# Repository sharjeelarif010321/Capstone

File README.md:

# Capstone
Final year capstone project

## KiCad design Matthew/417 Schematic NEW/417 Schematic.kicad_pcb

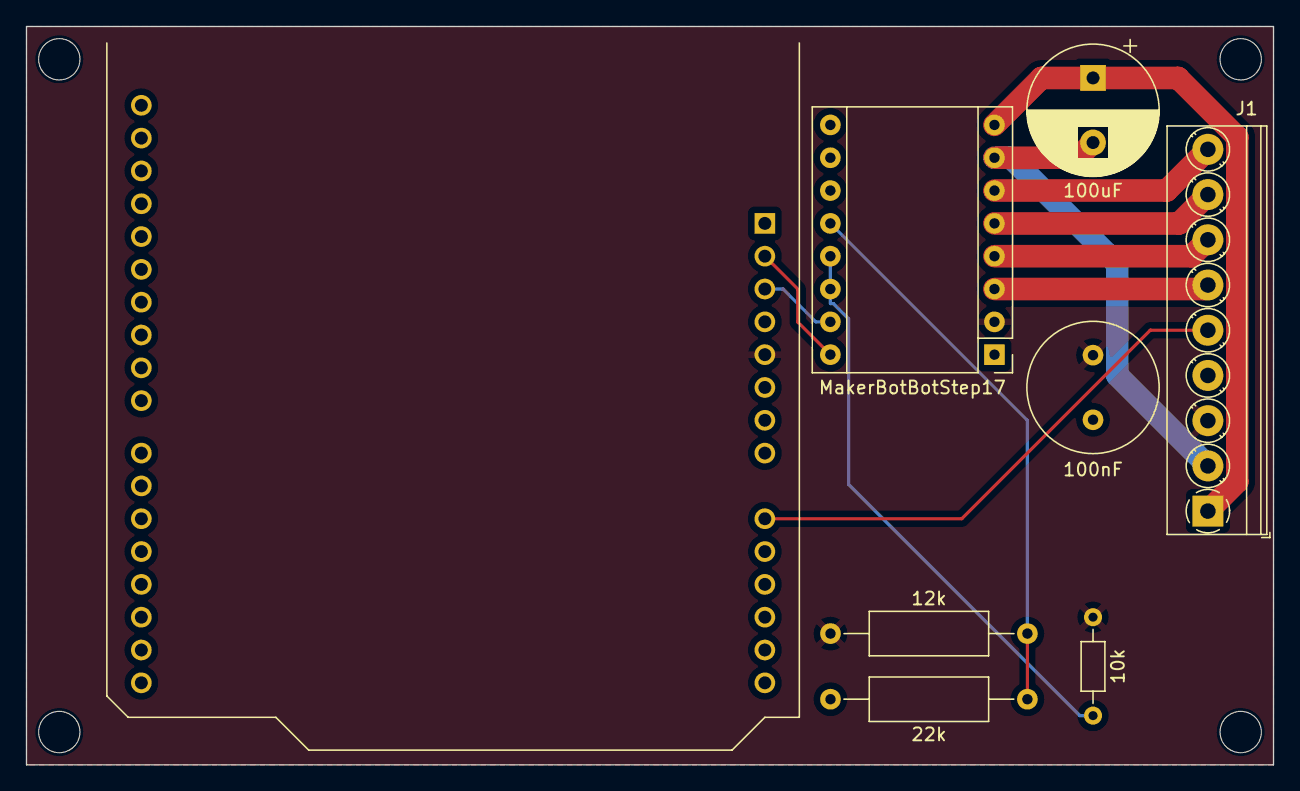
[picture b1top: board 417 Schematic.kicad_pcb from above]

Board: 2 copper layers, 96.5 x 57.2 mm, 12 parts (0 on the bottom side), 13 nets.

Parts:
10k: 10k; R_Axial_DIN0204_L3.6mm_D1.6mm_P7.62mm_Horizontal
12k: 12k; R_Axial_DIN0309_L9.0mm_D3.2mm_P15.24mm_Horizontal
22k: 22k; R_Axial_DIN0309_L9.0mm_D3.2mm_P15.24mm_Horizontal
100nF: physically close to board; C_Radial_D10.0mm_H12.5mm_P5.00mm
100uF: physically close to board; CP_Radial_D10.0mm_P5.00mm
A1: Arduino_UNO_R3
J1: Screw_Terminal_01x09; TerminalBlock_Phoenix_PT-1,5-9-3.5-H_1x09_P3.50mm_Horizontal
MakerBotBotStep17: A4982; Pololu_Breakout-16_15.2x20.3mm
REF01, REF02, REF03, REF04: MountingHole_3.2mm_M3

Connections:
+5V: 10k.1, 12k.1, 100nF.1, A1.5 (+5V), J1.3, MakerBotBotStep17.2 (VDD)
GND: 22k.2, 100nF.2, A1.6 (GND), A1.7 (GND), A1.29 (GND), J1.4, MakerBotBotStep17.1 (GND)
unnamed: A1.9 (A0), J1.5
unnamed: A1.2 (IOREF), MakerBotBotStep17.16 (DIR)
unnamed: A1.3 (~RESET), MakerBotBotStep17.15 (STEP)
unnamed: 100uF.1, J1.1, MakerBotBotStep17.8 (VMOT)
unnamed: 100uF.2, J1.2, MakerBotBotStep17.7 (GND)
unnamed: J1.6, MakerBotBotStep17.3 (1B)
unnamed: J1.7, MakerBotBotStep17.4 (1A)
unnamed: J1.8, MakerBotBotStep17.5 (2A)
unnamed: J1.9, MakerBotBotStep17.6 (2B)
unnamed: 12k.2, 22k.1, MakerBotBotStep17.12 (VR)
unnamed: 10k.2, MakerBotBotStep17.13 (~RESET), MakerBotBotStep17.14 (~SLEEP)

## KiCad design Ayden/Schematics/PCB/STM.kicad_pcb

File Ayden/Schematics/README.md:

This directory contains all schematics for the Baby Safety Subsystem, created in KiCAD.
<br>
<br>
**/PCB/** is the schematic used to design the PCB.
<br>
<br>
**/PCB_backwards_STM/** is an identical schematic to the previous, with the STM32F103RB's footprint mirrored on the PCB layout.
This was the first layout for the PCB I created, but I realized that the rear pins on my STM32F103RB board were bent, which means the STM board would not have been able to mount to the PCB properly.
<br>
<br>
**/STM/** is the schematic that shows the entire circuit, including the layout of the pressure mat. Since the previous two schematics have only a terminal block, it is not easy to visualize the connection to the pressure mat. This schematic does not include any PCB layout.
<br>
<br>
**/Wearable/** is the schematic for the wearable heart rate and blood oxygen monitor. A PCB was not necessary for this schematic.
<br>
<br>
**/libraries/** contains the two custom libraries that were necessary for me to get proper footprints for all of my components.

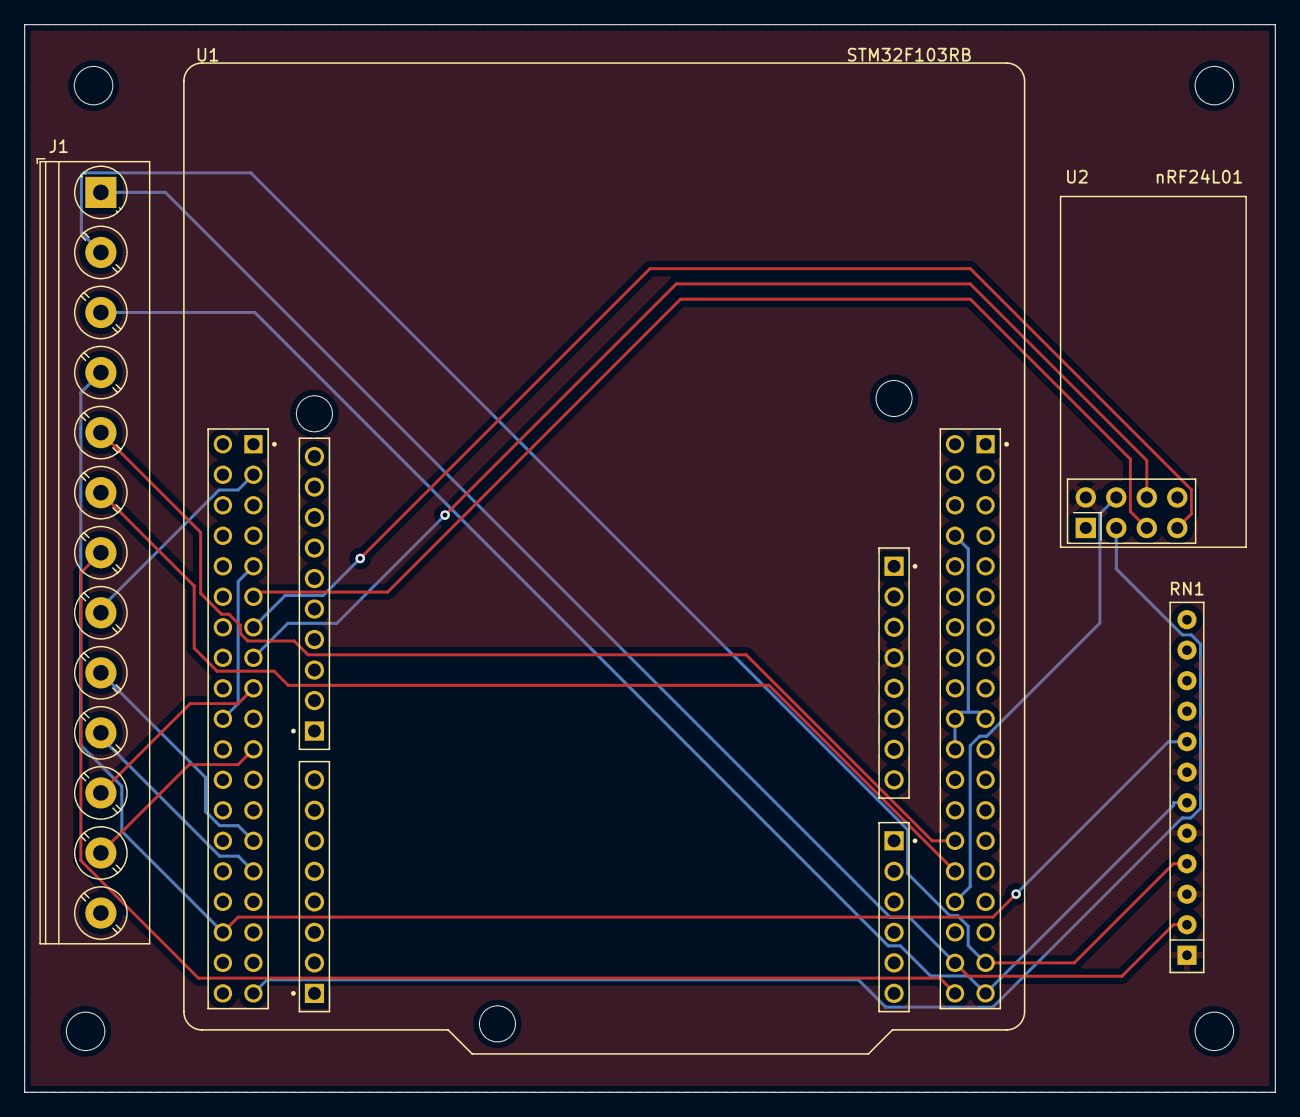
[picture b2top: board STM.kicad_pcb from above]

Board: 2 copper layers, 104.1 x 88.9 mm, 8 parts (1 on the bottom side), 21 nets.

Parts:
J1: Screw_Terminal_01x13; TerminalBlock_Phoenix_PT-1,5-13-5.0-H_1x13_P5.00mm_Horizont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
REF01, REF02, REF03, REF04: MountingHole_3.2mm_M3
RN1: R_Pack_SIP_1k; R_Array_SIP12
U1: NUCLEO-F103RB; ST_NUCLEO-F303RE
U2: NRF24L01_Breakout; nRF24L01_Breakout

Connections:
+3.3V: RN1.1 (R1.1), RN1.3 (R2.1), RN1.5 (R3.1), RN1.7 (R4.1), U1.CN6_4 (+3V3), U2.2 (VCC)
GND: J1.13, U1.CN6_6 (GND), U1.CN6_7 (GND), U2.1 (GND)
unnamed: J1.1, RN1.2 (R1.2), U1.CN7_36 (PC1)
unnamed: J1.2, RN1.4 (R2.2), U1.CN7_35 (PC2)
unnamed: J1.3, RN1.6 (R3.2), U1.CN7_37 (PC3)
unnamed: J1.4, RN1.8 (R4.2), U1.CN10_34 (PC4)
unnamed: U1.CN7_8 (GND_S1), U1.CN7_19 (GND_S1), U1.CN7_20 (GND_S1), U1.CN7_22 (GND_S1)
unnamed: J1.5, U1.CN7_28 (PA0)
unnamed: J1.6, U1.CN7_30 (PA1)
unnamed: U1.CN7_32 (PA4), U2.4 (~CSN)
unnamed: J1.7, U1.CN7_38 (PC0)
unnamed: J1.8, U1.CN10_3 (PB8)
unnamed: U1.CN10_11 (PA5), U2.5 (SCK)
unnamed: U1.CN10_13 (PA6), U2.7 (MISO)
unnamed: U1.CN10_15 (PA7), U2.6 (MOSI)
unnamed: J1.11, U1.CN10_17 (PB6)
unnamed: U1.CN10_9 (GND_S2), U1.CN10_20 (GND_S2)
unnamed: J1.12, U1.CN10_21 (PA9)
unnamed: J1.9, U1.CN10_27 (PB4)
unnamed: J1.10, U1.CN10_29 (PB5)
unnamed: U1.CN10_37 (PA3), U2.3 (CE)

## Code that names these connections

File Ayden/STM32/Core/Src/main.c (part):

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  GPIO_InitStruct.Pull = GPIO_NOPULL;
  HAL_GPIO_Init(B1_GPIO_Port, &GPIO_InitStruct);

  /*Configure GPIO pins : PC0 PC8 */
  GPIO_InitStruct.Pin = GPIO_PIN_0|GPIO_PIN_8;
  GPIO_InitStruct.Mode = GPIO_MODE_OUTPUT_PP;
  GPIO_InitStruct.Pull = GPIO_NOPULL;
  GPIO_InitStruct.Speed = GPIO_SPEED_FREQ_LOW;
  HAL_GPIO_Init(GPIOC, &GPIO_InitStruct);

  /*Configure GPIO pins : PA0 PA1 PA3 PA4 */
  GPIO_InitStruct.Pin = GPIO_PIN_0|GPIO_PIN_1|GPIO_PIN_3|GPIO_PIN_4;
  GPIO_InitStruct.Mode = GPIO_MODE_OUTPUT_PP;
  GPIO_InitStruct.Pull = GPIO_NOPULL;
  GPIO_InitStruct.Speed = GPIO_SPEED_FREQ_LOW;
  HAL_GPIO_Init(GPIOA, &GPIO_InitStruct);

  /*Configure GPIO pins : PB4 PB5 PB6 PB8 */
  GPIO_InitStruct.Pin = GPIO_PIN_4|GPIO_PIN_5|GPIO_PIN_6|GPIO_PIN_8;
  GPIO_InitStruct.Mode = GPIO_MODE_OUTPUT_PP;
  GPIO_InitStruct.Pull = GPIO_NOPULL;
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
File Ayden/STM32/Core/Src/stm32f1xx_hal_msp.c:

/* USER CODE BEGIN Header */
/**
  ******************************************************************************
  * @file         stm32f1xx_hal_msp.c
  * @brief        This file provides code for the MSP Initialization
  *               and de-Initialization codes.
  ******************************************************************************
  * @attention
  *
  * Copyright (c) 2023 STMicroelectronics.
  * All rights reserved.
  *
  * This software is licensed under terms that can be found in the LICENSE file
  * in the root directory of this software component.
  * If no LICENSE file comes with this software, it is provided AS-IS.
  *
  ******************************************************************************
  */
/* USER CODE END Header */

/* Includes ------------------------------------------------------------------*/
#include "main.h"
/* USER CODE BEGIN Includes */

/* USER CODE END Includes */

/* Private typedef -----------------------------------------------------------*/
/* USER CODE BEGIN TD */

/* USER CODE END TD */

/* Private define ------------------------------------------------------------*/
/* USER CODE BEGIN Define */

/* USER CODE END Define */

/* Private macro -------------------------------------------------------------*/
/* USER CODE BEGIN Macro */

/* USER CODE END Macro */

/* Private variables ---------------------------------------------------------*/
/* USER CODE BEGIN PV */

/* USER CODE END PV */

/* Private function prototypes -----------------------------------------------*/
/* USER CODE BEGIN PFP */

/* USER CODE END PFP */

/* External functions --------------------------------------------------------*/
/* USER CODE BEGIN ExternalFunctions */

/* USER CODE END ExternalFunctions */

/* USER CODE BEGIN 0 */

/* USER CODE END 0 */
/**
  * Initializes the Global MSP.
  */
void HAL_MspInit(void)
{
  /* USER CODE BEGIN MspInit 0 */

  /* USER CODE END MspInit 0 */

  __HAL_RCC_AFIO_CLK_ENABLE();
  __HAL_RCC_PWR_CLK_ENABLE();

  /* System interrupt init*/

  /** NOJTAG: JTAG-DP Disabled and SW-DP Enabled
  */
  __HAL_AFIO_REMAP_SWJ_NOJTAG();

  /* USER CODE BEGIN MspInit 1 */

  /* USER CODE END MspInit 1 */
}

/**
* @brief ADC MSP Initialization
* This function configures the hardware resources used in this example
* @param hadc: ADC handle pointer
* @retval None
*/
void HAL_ADC_MspInit(ADC_HandleTypeDef* hadc)
{
  GPIO_InitTypeDef GPIO_InitStruct = {0};
  if(hadc->Instance==ADC1)
  {
  /* USER CODE BEGIN ADC1_MspInit 0 */

  /* USER CODE END ADC1_MspInit 0 */
    /* Peripheral clock enable */
    __HAL_RCC_ADC1_CLK_ENABLE();

    __HAL_RCC_GPIOC_CLK_ENABLE();
    /**ADC1 GPIO Configuration
    PC1     ------> ADC1_IN11
    PC2     ------> ADC1_IN12
    PC3     ------> ADC1_IN13
    PC4     ------> ADC1_IN14
    */
    GPIO_InitStruct.Pin = GPIO_PIN_1|GPIO_PIN_2|GPIO_PIN_3|GPIO_PIN_4;
    GPIO_InitStruct.Mode = GPIO_MODE_ANALOG;
    HAL_GPIO_Init(GPIOC, &GPIO_InitStruct);

  /* USER CODE BEGIN ADC1_MspInit 1 */

  /* USER CODE END ADC1_MspInit 1 */
  }

}

/**
* @brief ADC MSP De-Initialization
* This function freeze the hardware resources used in this example
* @param hadc: ADC handle pointer
* @retval None
*/
void HAL_ADC_MspDeInit(ADC_HandleTypeDef* hadc)
{
  if(hadc->Instance==ADC1)
  {
  /* USER CODE BEGIN ADC1_MspDeInit 0 */

  /* USER CODE END ADC1_MspDeInit 0 */
    /* Peripheral clock disable */
    __HAL_RCC_ADC1_CLK_DISABLE();

    /**ADC1 GPIO Configuration
    PC1     ------> ADC1_IN11
    PC2     ------> ADC1_IN12
    PC3     ------> ADC1_IN13
    PC4     ------> ADC1_IN14
    */
    HAL_GPIO_DeInit(GPIOC, GPIO_PIN_1|GPIO_PIN_2|GPIO_PIN_3|GPIO_PIN_4);

  /* USER CODE BEGIN ADC1_MspDeInit 1 */

  /* USER CODE END ADC1_MspDeInit 1 */
  }

}

/**
* @brief SPI MSP Initialization
* This function configures the hardware resources used in this example
* @param hspi: SPI handle pointer
* @retval None
*/
void HAL_SPI_MspInit(SPI_HandleTypeDef* hspi)
{
  GPIO_InitTypeDef GPIO_InitStruct = {0};
  if(hspi->Instance==SPI1)
  {
  /* USER CODE BEGIN SPI1_MspInit 0 */

  /* USER CODE END SPI1_MspInit 0 */
    /* Peripheral clock enable */
    __HAL_RCC_SPI1_CLK_ENABLE();

    __HAL_RCC_GPIOA_CLK_ENABLE();
    /**SPI1 GPIO Configuration
    PA5     ------> SPI1_SCK
    PA6     ------> SPI1_MISO
    PA7     ------> SPI1_MOSI
    */
    GPIO_InitStruct.Pin = GPIO_PIN_5|GPIO_PIN_7;
    GPIO_InitStruct.Mode = GPIO_MODE_AF_PP;
    GPIO_InitStruct.Speed = GPIO_SPEED_FREQ_HIGH;
    HAL_GPIO_Init(GPIOA, &GPIO_InitStruct);

    GPIO_InitStruct.Pin = GPIO_PIN_6;
    GPIO_InitStruct.Mode = GPIO_MODE_INPUT;
    GPIO_InitStruct.Pull = GPIO_NOPULL;
    HAL_GPIO_Init(GPIOA, &GPIO_InitStruct);

  /* USER CODE BEGIN SPI1_MspInit 1 */

  /* USER CODE END SPI1_MspInit 1 */
  }

}

/**
* @brief SPI MSP De-Initialization
* This function freeze the hardware resources used in this example
* @param hspi: SPI handle pointer
* @retval None
*/
void HAL_SPI_MspDeInit(SPI_HandleTypeDef* hspi)
{
  if(hspi->Instance==SPI1)
  {
  /* USER CODE BEGIN SPI1_MspDeInit 0 */

  /* USER CODE END SPI1_MspDeInit 0 */
    /* Peripheral clock disable */
    __HAL_RCC_SPI1_CLK_DISABLE();

    /**SPI1 GPIO Configuration
    PA5     ------> SPI1_SCK
    PA6     ------> SPI1_MISO
    PA7     ------> SPI1_MOSI
    */
    HAL_GPIO_DeInit(GPIOA, GPIO_PIN_5|GPIO_PIN_6|GPIO_PIN_7);

  /* USER CODE BEGIN SPI1_MspDeInit 1 */

  /* USER CODE END SPI1_MspDeInit 1 */
  }

}

/**
* @brief UART MSP Initialization
* This function configures the hardware resources used in this example
* @param huart: UART handle pointer
* @retval None
*/
void HAL_UART_MspInit(UART_HandleTypeDef* huart)
{
  GPIO_InitTypeDef GPIO_InitStruct = {0};
  if(huart->Instance==USART1)
  {
  /* USER CODE BEGIN USART1_MspInit 0 */

  /* USER CODE END USART1_MspInit 0 */
    /* Peripheral clock enable */
    __HAL_RCC_USART1_CLK_ENABLE();

    __HAL_RCC_GPIOA_CLK_ENABLE();
    /**USART1 GPIO Configuration
    PA9     ------> USART1_TX
    PA10     ------> USART1_RX
    */
    GPIO_InitStruct.Pin = GPIO_PIN_9;
    GPIO_InitStruct.Mode = GPIO_MODE_AF_PP;
    GPIO_InitStruct.Speed = GPIO_SPEED_FREQ_HIGH;
    HAL_GPIO_Init(GPIOA, &GPIO_InitStruct);

    GPIO_InitStruct.Pin = GPIO_PIN_10;
    GPIO_InitStruct.Mode = GPIO_MODE_INPUT;
    GPIO_InitStruct.Pull = GPIO_NOPULL;
    HAL_GPIO_Init(GPIOA, &GPIO_InitStruct);

  /* USER CODE BEGIN USART1_MspInit 1 */

  /* USER CODE END USART1_MspInit 1 */
  }

}

/**
* @brief UART MSP De-Initialization
* This function freeze the hardware resources used in this example
* @param huart: UART handle pointer
* @retval None
*/
void HAL_UART_MspDeInit(UART_HandleTypeDef* huart)
{
  if(huart->Instance==USART1)
  {
  /* USER CODE BEGIN USART1_MspDeInit 0 */

  /* USER CODE END USART1_MspDeInit 0 */
    /* Peripheral clock disable */
    __HAL_RCC_USART1_CLK_DISABLE();

    /**USART1 GPIO Configuration
    PA9     ------> USART1_TX
    PA10     ------> USART1_RX
    */
    HAL_GPIO_DeInit(GPIOA, GPIO_PIN_9|GPIO_PIN_10);

  /* USER CODE BEGIN USART1_MspDeInit 1 */

  /* USER CODE END USART1_MspDeInit 1 */
  }

}

/* USER CODE BEGIN 1 */

/* USER CODE END 1 */

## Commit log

2022-11-21 Test commit
2022-11-21 test for sharjeel
2022-11-21 inclass activity
2023-01-19 Initial commit with basic heart rate/SpO2 monitoring working
2023-01-19 began adding code for nRF24L01
2023-01-25 Wireless comms between STM and Arduino working
2023-01-25 Added low-power code to Arduino and debug LED for STM32
2023-01-27 Added more power savings code (clock divider, powerdown)
2023-02-02 Created schematic for wearable device
2023-02-02 Created schematic for STM32F103RB connections
2023-02-03 Worked on more power-saving code for Arduino
2023-02-12 Added code to view analog data from 3x3 prototype pressure mat
2023-02-12 Added prototype 3x3 pressure mat to STM schematic
2023-02-13 Changed from pull-down to pull-up resistors on sensor mat. Also added helper functions
2023-02-13 Edited schematic to reflect new pull-up configuration
2023-02-17 Started writing code to concatenate data into single buffer
2023-03-01 Added code to sweep ADC for full-size pressure mat
2023-03-01 Updated schematic to include full-size pressure mat
2023-03-01 Added code to process data and prepare for sending over UART
2023-03-01 Added code to transmit data over UART
2023-03-02 Added code to utilize TPL5111 timer
2023-03-02 Included TPL5111 timer in schematic
2023-03-02 Changed organization of data buffers
2023-03-02 Set D08 low at start
2023-03-03 Add libraries for KiCad
2023-03-03 Create schematics and PCB layouts
2023-03-03 Added currently completed libraries and functions
    Currently finished libraries with functions and descriptions included
2023-03-03 Create readme.txt.txt
    Created my folder for the capstone
2023-03-03 Created dataProcessSTMTest.py
    Created script to translate serial data from STM to Array to be parsed on Pi
2023-03-04 Add UART drivers
2023-03-04 Add .gitignore files
2023-03-04 Update schematic/PCB to include connection for common GND
2023-03-07 Changed terminating character in UART comms to newline
2023-03-10 Utilize TPL5111 on pin 7 and increase reliability of wearable
2023-03-10 Update schematic to reflect true construction of circuit
2023-03-10 Resolve deltas
2023-03-10 Test code to establish serial comms through USB
2023-03-13 Adding schematic for Arduino PCB
2023-03-22 Created directory for scripts used in training model
2023-03-22 added preprocessDataset.py, splitDataSet.py, testModel.py
    preprocessDataset.py - preprocesses the data to make entire data set uniform.
    splitDataSet.py - Creates classes from dataset off images based off labels
    testModel.py - Tests model off test dataset.
2023-03-23 Added more layers for accuracy
2023-03-23 Increased trials for more accuracy
2023-03-23 Organized schematic for project demo
2023-03-23 Organize schematic for project demo
2023-03-23 Updated schematic for project demo
2023-03-23 Updated schematic information on plot
2023-03-23 Changed to 6 trials before powering down
2023-03-23 Force use of software UART
2023-04-03 Add comments
2023-04-08 3 speed
    The motor runs at 3 different speeds based on the microphone input
2023-04-08 3 speed UART
    Motor runs at three different speed based on microphone input and has the beginning of UART Communication
2023-04-08 28BYJ stepper
    Code to run a 28BYJ stepper motor
2023-04-08 Test code
    Testing motor alternatives
2023-04-08 Interrupt
    Testing the use of interrupts
2023-04-08 AccelStepper Library
    The contents of the AccelStepper Library
2023-04-08 Motor control test
    Tested using a for loop for motor duration
2023-04-08 Tested using AccelStepper header
    attempted to use the AccelStepper library
2023-04-08 Read analog values
    only read the analog value and didn't convert to decibel
2023-04-08 Motor testing code
    Changes the speed for the motor 3 times and then resets. runs continuously
2023-04-08 Motor mic test
    Tested whether or not the motor would turn on based on the microphone input
2023-04-08 Attempt to make motor running higher priority
    Attempted to make the motor running a higher priority than the audio sampling
2023-04-08 Interrupt test again
    attempted to test interrupts again
2023-04-08 Microphone sampling code
    Code to sample the audio input into the microphone and then converts the input to decibels
2023-04-08 AccelStepper test again
    Testing using the AccelStepper library again
2023-04-11 Restructured file system. Added dataAugment.py with header within file
2023-04-11 Added trainModel.py with revision history
2023-04-11 Added testModel.py with revision history
2023-04-11 Added createTFLite.py with revision history
2023-04-11 Added test data for all four version of baby posture model including accuracy results
2023-04-11 Added captureData.py with revision history
2023-04-11 Update splitDataSet.py with revision history
2023-04-11 Added models that were trained
2023-04-11 Updated main Algorithm Scripts with latest code. Also included descriptions
2023-04-11 Fixed directory naming conventions and added training plots for each model version
2023-04-11 Added schematics and block diagrams created for each aspect of the algorithm
2023-05-12 SafeSnooze iOS Application
